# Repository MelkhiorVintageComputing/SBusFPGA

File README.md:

# A FPGA on a SBus card...

## Goal

The goal of this repository is to be able to interface a modern (2020 era) [FPGA](https://en.wikipedia.org/wiki/Field-programmable_gate_array) with a [SBus](https://en.wikipedia.org/wiki/SBus) host. SBus was widely used in SPARCstation and compatibles system in the first half of the 90s. It was progressively displaced by PCI from the mid-90s onward, and is thoroughly obsolete.

So unless you're a retrocomputing enthusiast with such a machine, this is useless. To be honest, even if you are such an enthusiast, it's probably not that useful...

I'm a software guy and know next to nothing about hardware design, so this is very much a work-in-progress and is likely full of rookie mistakes.

To save on PCB cost, the board is smaller than a 'true' SBus board; the hardware directory includes an OpenSCAD 3D-printable extension to make the board compliant to the form factor (visible in the pictures in 'Pictures') (need to be updated for V1.3).

## Current status

2023-10-07: V1.3 in testing.

2022-11-18: V1.2 seems stable, with various subsets of the peripherals described below. It only lacks a proper video output, such as the one available in the [NuBusFPGA](https://github.com/rdolbeau/NuBusFPGA). Unfortunately the FPGA board used in V1.0/V1.2 (ZTex 2.13) doesn't have enough available I/O to add it in addition to the already existing I/Os.

## The hardware

Directory 'sbus-to-ztex'

The V1.2 custom board is a SBus-compliant (I hope...) board, designed to receive a [ZTex USB-FPGA Module 2.13](https://www.ztex.de/usb-fpga-2/usb-fpga-2.13.e.html) as a daughterboard. The ZTex module contains the actual FPGA (Artix-7), some RAM, programming hardware, etc. The SBus board contains level-shifters ICs to interface between the SBus signals and the FPGA, a serial header, a Led, a JTAG header, a micro-sd card slot, a USB micro-B connector, and a (Pmod)[https://digilent.com/shop/boards-and-components/system-board-expansion-modules/pmods/] connector. It supports every SBus feature except the optional parity (i.e. it can do both slave and master modes) and interrupt level 1 to 6 are connected.

The V1.3 custom board is similar to V1.2 but reorganized & redesigned to have all components on the top side and cleaner routing. It also loose the led, setial header & micro-sd to gain a HDMI connector. The USB micro-B is still present, and the PMod was rewired to carry 8 length-matched differential pairs.

The PCB was designed with Kicad 5.0 for V1.2, 5.1 for V1.3.

## The gateware (Migen)

Directory 'sbus-to-ztex-gateware-migen'

### Intro

The gateware is written in the Migen language, choosen because that's what [Litex](https://github.com/enjoy-digital/litex/) uses.
It implements a simple CPU-less Litex SoC built around a Wishbone bus, with a custom bridge between the SBus and the Wishbone.

A ROM, a SDRAM controller ([litedram](https://github.com/enjoy-digital/litedram) to the on-board DDR3), a TRNG (using the [NeoRV32](https://github.com/stnolting/neorv32) TRNG), an USB OHCI (host controller, using the Litex wrapper around the [SpinalHDL](https://github.com/SpinalHDL/SpinalHDL) implementation), a Curve25519 Crypto Engine (taken from the [Betrusted.IO](https://betrusted.io/) project and expanded to add AES and GCM support) and a Litex micro-sd controller can be connected to that bus. As a test feature for the Pmod connector, a bw2/cg3/cg6-compatible framebuffer can be implemented using a custom RGA222 VGA Pmod (with serious color quality restrictions). The 'Goblin' framebuffer (a multi-depth gramebuffer) can also be used with the VGA Pmod, using 8-bits depth in the console or accelerated 24-bits in X11. Alternatively on the Pmod en I2C bus (the Betrusted.IO wrapper around an OpenCore controller) can be implemented for e.g. temperature control.

### Details

Master access to the SBus by the host are routed to the Wishbone to access the various CSRs / control registers of the devices.

The ROM exposes the devices' existence and specifications to the host, initializes the embedded SDRAM controller (but assuming known values, the NetBSD driver can also optionally initialize the SDRAM via proper calibration), enables FB support on the bw2/cg3/cg6 (last one with accelerated scrolling), and has support for RO access to the sdcard such enabling booting.

The USB OHCI DMA (USB 1.1) is bridged from the Wishbone to the SBus by having the physical addresses of the Wishbone (that match the virtual addresses from NetBSD DVMA allocations) to the bridge (see also 'Sun4m vs. Sun4c' below). Reads are buffered by block of 16 bytes; currently writes are unbuffered (and somewhat slow, as they need a full SBus master cycle for every transaction of 32 bits or less). The standard NetBSD OHCI driver is used, with just a small custom SBus-OHCI driver mirroring the PCI-OHCI one. It uses the interrupt level 4 by default. It connects to the micro-B USB connector, an a cable such as [this one](https://www.startech.com/en-us/cables/uusbotgra) allows to expose a conventional USB type A connector for either an external (preferably self-powered) USB Hub or a single low-power device.

The SDRAM has its own custom DMA controller, using native Litedram interface to the memory, and some FIFO to/from the SBus. A custom NetBSD driver exposes it as a drive on which you can swap. It's also usable as a 'fast', volatile disk (for e.g. /tmp or similar temporary filesystem). It can use a interrupt line, but software support isn't there yet (only synchronous polling).

The micro-sd card controller is using a similar driver to the SDRAM, so is also currently limited to sychronous polling and lack of support for interrupts (or removability). It also has some level of support in the PROM, enabling it as a boot device (of course using a NetBSD kernel with appropriate support). For its DMA engine, the micro-sd controller uses the same Wishbone/SBus bridge as designed for the USB OHCI.

The TRNG has a NetBSD driver to add entropy to the entropy pool.

The Curve25519 Engine currently exposes an IOCTL to do the computation, which has yet to be integrated usefully in e.g. OpenSSL. It could use a interrupt line, but it's not yet implemented in software. The load/store unit used the same Wishbone/SBus bridge as designed for the USB OHCI.

The I2C bus currently uses a custom Pmod to plug an AT30TS74 temperature sensor (LM75-compatible, usable with 'envstat' in NetBSD), but should support most/all I2C devices supported by NetBSD.

The bw2/cg3/cg6 emulation requires the custom Pmod on V1.2, and colors are vert limited at 2 bits per channel, so it's for testing mostly. V1.3 has a HDMI connector using DVI signaling and so support the full color range. bw2/cg3 can work as a PROM console, a NetBSD console, and with X11, all as an non-accelerated framebuffer. Resolution can be arbitrary but is fixed in the bitstream at synthesis time, the current design can go up to 1920x1080@60Hz. cg6 emulation is similar but uses a micro-coded VexRiscv core to emulate some of the cg6 hardware acceleration, enough to accelerate the PROM console, the NetBSD console and X11 EXA acceleration in NetBSD 9.0. The cg3/cg6 emulation was also tested with the original PROM code for cg3 (501-1415) and TGX+ (501-2253), but this requires hardware-based initialization (instead of PROM-based) and prevent exposing other devices in the PROM code.

The 'Goblin' framebuffer works similarly to the cg6 emulation (from which it has grown for the NuBusFPGA), but is using 24-bits in X11 (switching in a way similar to the cg14) and has some Xrender acceleration. Using the same 2-bits-per-channel VGA Pmod, it also suffers from color limitations ob V1.2. It also uses tje HDMI connector on V1.3.

### Special Notes

Currently the design uses a Wishbone Crossbar Interconnect from Litex instead of a Shared Interconnect, as for some reason using a Shared Interconnect causes issues between devices (disabling the USB OHCI seem also to solve the issue, it generates a lot of cycles on the buses). I might be misusing Wishbone. With the Crossbar, all devices are usable simultaneously if they fit in the FPGA.

As not everything lives in the same clock domain, the design also use a Wishbone CDC, a wrapper around the one from [Verilog Wishbone Components](https://github.com/alexforencich/verilog-wishbone).

## The software

Directory 'NetBSD'

Some basic drivers for NetBSD 9.0/sparc to enable the devices as described above. bw2/cg3/cg6 uses unmodifed NetBSD drivers. USB OHCI needs only a SBus-OHCI layer, the NetBSD OHCI driver and USB stack are used unmodified.

## Sun4m vs. Sun4c

The current DMA scheme for Wishbone devices (USB OHCI, micro-sd, ...) works fine on sun4m machine with an IOMMU (SPARCstation 4, 5, 10, 20 ...). NetBSD will always allocate the DVMA buffers in the range from IOMMU_DVMA_BASE to the end of the memory space (IOMMU_DVMA_BASE is 0xFC000000 by default, and that must include 0xFF000000 to the end which are the only virtual addresses accessible by some legacy devices used in some SPARCstation). However, sun4c machine (SPARCstation 1, 2, IPC, IPX, ...) do not have an IOMMU, and have no virtual address restriction for non-legacy device. And the NetBSD kernel takes advantage of this, I have observed DVMA buffers mapped to prefix 0xF4 and 0xF3. Extending the mapping for the DVMA bridge in Wishbone to the full 0xF prefix enable booting from sd-card on an IPX, but I'm not sure this is reliable.

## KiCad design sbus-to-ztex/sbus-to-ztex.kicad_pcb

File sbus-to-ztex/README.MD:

# A FPGA on a SBus card...

## Goal

The goal of this repository is to be able to interface a modern (2020 era) [FPGA](https://en.wikipedia.org/wiki/Field-programmable_gate_array) with a [SBus](https://en.wikipedia.org/wiki/SBus) host. SBus was widely used in SPARCstation and compatibles system in the first halt of the 90s. It was progressively displaced by PCI from the mid-90s onward.

So unless you're a retrocomputing enthusiast with such a machine, this is useless. To be honest, even if you are such an enthusiast, it's probably not that useful...

I'm a software guy and know next to nothing about hardware design, so this is very much a work-in-progress and is likely full of rookie mistakes.

## The hardware

The board is a SBus-compliant (I hope...) board, designed to receive a ZTex USB-FPGA Module 2.13 as a dauguterboard. The ZTex module contains the actual FPGA (Artix-7), some RAM, programming hardware, etc. The SBus board contains level-shifters ICs to interface between the SBus signals and the FPGA, some Leds, a JTAG header, and a micro-sd card slot.

## The gateware

The function embedded in the FPGA currently includes the PROM, lighting Led to display a 32-bits value, and a GHASH MAC (128 polynomial accumulator, used for the AES-GCM encryption scheme). The device is a fairly basic scale, but should be able to read from the PROM and read/write from the GCM space with any kind of SBus burst (1, 2, 4, 8 or 16 words).

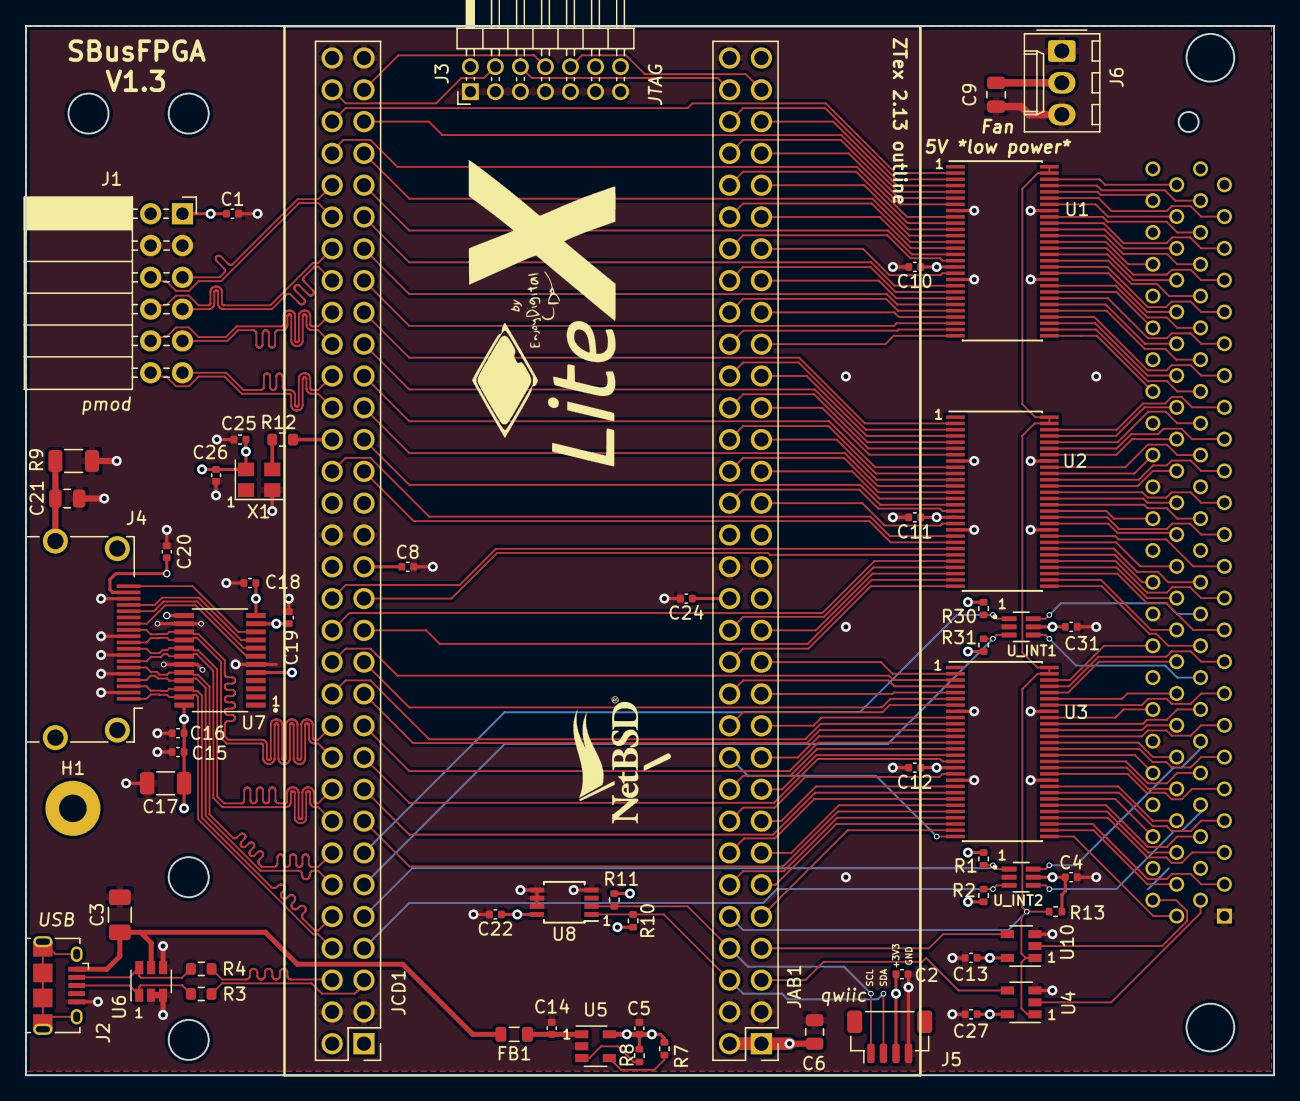
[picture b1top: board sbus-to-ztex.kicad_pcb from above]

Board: 4 copper layers, 99.7 x 83.8 mm, 64 parts (1 on the bottom side), 199 nets.

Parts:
C1, C2: 100nF; C_0402_1005Metric
C3: 100uF 1206 (officially 150 uF ? could be >= 100 u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; C_1206_3216Metric
C4, C5, C8, C10, C11, C12, C13, C14, C15, C18, C19, C20, C24, C25, C27, C31: 100nF 0402; C_0402_1005Metric
C6, C9: 47uF 0805; C_0805_2012Metric
C16, C22, C26: 10nF 0402; C_0402_1005Metric
C17: 47uF 10V 1206; C_1206_3216Metric
C21: 10nF 1kV 0805; C_0805_2012Metric
FB1: Ferrite_Bead_Small; L_0805_2012Metric
GRAPHIC1: LogoLitex; litex_logo
GRAPHIC2: LogoNetBSD; netbsd_logo
H1: MountingHole_Pad; MountingHole_2.2mm_M2_Pad
J1: A2541HWR-2x6P (Pmod 2x6 F R); PinSocket_2x06_P2.54mm_Horizontal
J2: 10118194-0001LF (USB micro-B); USB_Micro-B_Amphenol_10118194_Horizontal
J3: Conn_02x07_Odd_Even; PinHeader_2x07_P2.00mm_Horizontal_For_SeeedStudio
J4: 10029449-111RLF (HDMI A); HDMI_A_Amphenol_10029449-111
J5: Conn_01x04_Male; JST_SH_BM04B-SRSS-TB_1x04-1MP_P1.00mm_Vertical
J6: Conn_01x03_Male; Molex_KK-254_AE-6410-03A_1x03_P2.54mm_Vertical
JAB1: ZTEX_AB-ztex_AB; PinHeader_2x32_P2.54mm_Vertical_For_SeeedStudio
JCD1: ZTEX_CD-ztex_CD; PinHeader_2x32_P2.54mm_Vertical_For_SeeedStudio
R1, R2, R7, R8, R13, R30, R31: 10k; R_0402_1005Metric
R3, R4, R12: 27; R_0603_1608Metric
R9: 1M 500V 1206; R_1206_3216Metric
R10, R11: 5.6k; R_0402_1005Metric
SBus1: SBus; FCN-234P096-GY
U1, U2, U3: SN74CB3T16211DGGR; TSSOP-56_6.1x14mm_P0.5mm_For_SeeedStudio
U4, U10: 74CB3T1G125; SOT-23-5
U5: TPS2051CDBV; SOT-23-5
U6: SRV05-4; SOT-23-6
U7: TPD12S016PWR; SOP65P640X120-24N
U8: PCT2075DP; TSSOP-8_3x3mm_P0.65mm_ForSeeedStudio
U_INT1, U_INT2: 74LVC2G07; SOT65P210X110-6N
X1: ASE-xxxMHz; Oscillator_SMD_Abracon_ASE-4Pin_3.2x2.5mm

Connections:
+3V3: C1.1, C2.1, C4.1, C8.1, C10.1, C11.1, C12.1, C13.1, C15.1, C16.1, C17.1, C18.1, C22.1, C24.1, C25.1, C26.1, C27.1, C31.1, J1.1, J1.2, J5.3, JAB1.29, JAB1.30, JAB1.33, JAB1.34, JCD1.31, JCD1.32, JCD1.35, JCD1.36, R1.1, R2.1, R10.2, R11.2, R13.1, R30.1, R31.1, U1.17, U2.17, U3.17, U4.5, U7.5, U7.12, U7.24, U8.8, U10.5, U_INT1.5, U_INT2.5, X1.4
+5V: C5.1, C6.1, C9.1, C19.1, J6.2, JAB1.1, JAB1.2, R7.2, R8.2, SBus1.56, SBus1.64, SBus1.72, SBus1.80, SBus1.88, U5.5, U7.11
/B2B/JTAG_TCK: J3.6, JAB1.62
/B2B/JTAG_TDI: J3.10, JAB1.61
/B2B/JTAG_TDO: J3.8, JCD1.61
/B2B/JTAG_TMS: J3.4, JCD1.62
/B2B/JTAG_VIO: J3.2, JAB1.63
/USB/USB_D+: J2.3, R3.1, U6.1
/USB/USB_D-: J2.2, R4.1, U6.6
/USB/USB_EN: R7.1, U5.4
/USB/USB_FLT: R8.1, U5.3
/USB/VBus: C14.1, FB1.1, U5.1
/USB/VBus_USB0: C3.1, FB1.2, J2.1, U6.5
/hdmi/HDMI_5V: C20.1, J4.18, U7.13
/hdmi/cec_b: J4.13, U7.7
/hdmi/hpd_b: J4.19, U7.10
/hdmi/scl_b: J4.15, U7.8
/hdmi/sda_b: J4.16, U7.9
CLK_54_000: JCD1.40, R12.1
GND: C1.2, C2.2, C3.2, C4.2, C5.2, C6.2, C8.2, C9.2, C10.2, C11.2, C12.2, C13.2, C14.2, C15.2, C16.2, C17.2, C18.2, C19.2, C20.2, C21.2, C22.2, C24.2, C25.2, C26.2, C27.2, C31.2, J1.3, J1.4, J2.5, J3.1, J3.3, J3.5, J3.7, J3.9, J3.11, J3.13, J4.2, J4.5, J4.8, J4.11, J4.17, J5.4, J6.1, J6.3, JAB1.3, JAB1.4, JAB1.31, JAB1.32, JAB1.64, JCD1.3, JCD1.4, JCD1.33, JCD1.34, JCD1.63, JCD1.64, R9.2, SBus1.01, SBus1.52, SBus1.60, SBus1.68, SBus1.76, SBus1.84, SBus1.92, U1.8, U1.19, U1.38, U1.49, U2.8, U2.19, U2.38, U2.49, U3.8, U3.19, U3.38, U3.49, U4.3, U5.2, U6.2, U6.3, U6.4, U7.6, U7.14, U7.19, U8.4, U8.5, U8.6, U8.7, U10.3, U_INT1.2, U_INT2.2, X1.2
HDMI_CLK+: J4.10, JCD1.20, U7.16
HDMI_CLK-: J4.12, JCD1.22, U7.15
HDMI_D0+: J4.7, JCD1.16, U7.18
HDMI_D0-: J4.9, JCD1.18, U7.17
HDMI_D1+: J4.4, JCD1.12, U7.21
HDMI_D1-: J4.6, JCD1.14, U7.20
HDMI_D2+: J4.1, JCD1.8, U7.23
HDMI_D2-: J4.3, JCD1.10, U7.22
I2C0_SCL: J5.1, JAB1.8, R11.1, U8.2
I2C0_SDA: J5.2, JAB1.6, R10.1, U8.1
unnamed: R12.2, X1.3
PMOD-56+: J1.6, JCD1.54
PMOD-56-: J1.5, JCD1.56
PMOD-78+: J1.8, JCD1.52
PMOD-78-: J1.7, JCD1.50
PMOD-910+: J1.10, JCD1.48
PMOD-910-: J1.9, JCD1.46
PMOD-1112+: J1.12, JCD1.42
PMOD-1112-: J1.11, JCD1.44
SBUS_3V3_ACK[0]*: JAB1.48, U1.24
SBUS_3V3_ACK[1]*: JCD1.55, U1.15
SBUS_3V3_ACK[2]*: JAB1.57, U1.7
SBUS_3V3_AS*: JAB1.9, U3.27
SBUS_3V3_BG*: JAB1.7, U10.4
SBUS_3V3_BR*: JAB1.5, U4.4
SBUS_3V3_CLK: JAB1.20, U3.28
SBUS_3V3_D[00]: JAB1.12, U3.25
SBUS_3V3_D[01]: JCD1.15, U3.24
SBUS_3V3_D[02]: JAB1.13, U3.23
SBUS_3V3_D[03]: JAB1.14, U3.22
SBUS_3V3_D[04]: JCD1.17, U3.21
SBUS_3V3_D[05]: JAB1.15, U3.20
SBUS_3V3_D[06]: JAB1.16, U3.18
SBUS_3V3_D[07]: JCD1.19, U3.16
SBUS_3V3_D[08]: JAB1.17, U3.15
SBUS_3V3_D[09]: JAB1.18, U3.14
SBUS_3V3_D[10]: JCD1.21, U3.13
SBUS_3V3_D[11]: JAB1.19, U3.12
SBUS_3V3_D[12]: JCD1.23, U3.11
SBUS_3V3_D[13]: JCD1.24, U3.10
SBUS_3V3_D[14]: JAB1.21, U3.9
SBUS_3V3_D[15]: JAB1.22, U3.7
SBUS_3V3_D[16]: JCD1.25, U3.6
SBUS_3V3_D[17]: JAB1.23, U3.5
SBUS_3V3_D[18]: JAB1.24, U3.4
SBUS_3V3_D[19]: JCD1.26, U3.3
SBUS_3V3_D[20]: JAB1.25, U3.2
SBUS_3V3_D[21]: JAB1.26, U2.28
SBUS_3V3_D[22]: JCD1.27, U2.27
SBUS_3V3_D[23]: JAB1.27, U2.26
SBUS_3V3_D[24]: JAB1.28, U2.25
SBUS_3V3_D[25]: JCD1.28, U2.24
SBUS_3V3_D[26]: JCD1.29, U2.23
SBUS_3V3_D[27]: JCD1.30, U2.22
SBUS_3V3_D[28]: JCD1.37, U2.21
SBUS_3V3_D[29]: JCD1.38, U2.20
SBUS_3V3_D[30]: JAB1.35, U2.18
SBUS_3V3_D[31]: JAB1.36, U2.16
SBUS_3V3_EER*: JAB1.43, U2.4
SBUS_3V3_INT[2]*: JCD1.7, R2.2, U_INT2.3
SBUS_3V3_INT[3]*: JCD1.9, R1.2, U_INT2.1
SBUS_3V3_INT[4]*: JCD1.11, R31.2, U_INT1.3
SBUS_3V3_INT[5]*: JCD1.13, R30.2, U_INT1.1
SBUS_3V3_PA[00]: JAB1.40, U2.10
SBUS_3V3_PA[01]: JAB1.39, U2.11
SBUS_3V3_PA[02]: JAB1.41, U2.7
SBUS_3V3_PA[03]: JCD1.43, U2.9
SBUS_3V3_PA[04]: JCD1.45, U2.5
SBUS_3V3_PA[05]: JAB1.42, U2.6
SBUS_3V3_PA[06]: JCD1.47, U2.2
SBUS_3V3_PA[07]: JAB1.44, U2.3
SBUS_3V3_PA[08]: JAB1.46, U1.27
SBUS_3V3_PA[09]: JAB1.45, U1.28
SBUS_3V3_PA[10]: JAB1.47, U1.25
SBUS_3V3_PA[11]: JCD1.49, U1.26
SBUS_3V3_PA[12]: JAB1.49, U1.22
SBUS_3V3_PA[13]: JCD1.51, U1.23
SBUS_3V3_PA[14]: JCD1.53, U1.20
SBUS_3V3_PA[15]: JAB1.50, U1.21
SBUS_3V3_PA[16]: JAB1.52, U1.16
SBUS_3V3_PA[17]: JAB1.51, U1.18
SBUS_3V3_PA[18]: JAB1.54, U1.13
SBUS_3V3_PA[19]: JAB1.53, U1.14
SBUS_3V3_PA[20]: JAB1.55, U1.11
SBUS_3V3_PA[21]: JCD1.57, U1.12
SBUS_3V3_PA[22]: JCD1.58, U1.9
SBUS_3V3_PA[23]: JAB1.56, U1.10
SBUS_3V3_PA[24]: JCD1.59, U1.5
SBUS_3V3_PA[25]: JAB1.58, U1.6
SBUS_3V3_PA[26]: JAB1.60, U1.3
SBUS_3V3_PA[27]: JAB1.59, U1.4
SBUS_3V3_PPRD: JAB1.38, U2.13
SBUS_3V3_RST*: JCD1.60, U1.2
SBUS_3V3_SEL*: JAB1.11, U3.26
SBUS_3V3_SIZ[0]: JAB1.37, U2.14
SBUS_3V3_SIZ[1]: JCD1.39, U2.15
SBUS_3V3_SIZ[2]: JCD1.41, U2.12
SBUS_5V_ACK[0]*: SBus1.36, U1.33
SBUS_5V_ACK[1]*: SBus1.40, U1.41
SBUS_5V_ACK[2]*: SBus1.44, U1.48
SBUS_5V_AS*: SBus1.51, U3.30
SBUS_5V_BG*: SBus1.50, U10.2
SBUS_5V_BR*: SBus1.02, U4.2
SBUS_5V_CLK: SBus1.49, U3.29
SBUS_5V_D[00]: SBus1.05, U3.32
SBUS_5V_D[01]: SBus1.53, U3.33
SBUS_5V_D[02]: SBus1.06, U3.34
SBUS_5V_D[03]: SBus1.54, U3.35
SBUS_5V_D[04]: SBus1.07, U3.36
SBUS_5V_D[05]: SBus1.55, U3.37
SBUS_5V_D[06]: SBus1.09, U3.39
SBUS_5V_D[07]: SBus1.57, U3.40
SBUS_5V_D[08]: SBus1.10, U3.41
SBUS_5V_D[09]: SBus1.58, U3.42
SBUS_5V_D[10]: SBus1.11, U3.43
SBUS_5V_D[11]: SBus1.59, U3.44
SBUS_5V_D[12]: SBus1.13, U3.45
SBUS_5V_D[13]: SBus1.61, U3.46
SBUS_5V_D[14]: SBus1.14, U3.47
SBUS_5V_D[15]: SBus1.62, U3.48
SBUS_5V_D[16]: SBus1.15, U3.50
SBUS_5V_D[17]: SBus1.63, U3.51
SBUS_5V_D[18]: SBus1.65, U3.52
SBUS_5V_D[19]: SBus1.17, U3.53
SBUS_5V_D[20]: SBus1.66, U3.54
SBUS_5V_D[21]: SBus1.18, U2.29
SBUS_5V_D[22]: SBus1.67, U2.30
SBUS_5V_D[23]: SBus1.19, U2.31
SBUS_5V_D[24]: SBus1.69, U2.32
SBUS_5V_D[25]: SBus1.21, U2.33
SBUS_5V_D[26]: SBus1.70, U2.34
SBUS_5V_D[27]: SBus1.22, U2.35
SBUS_5V_D[28]: SBus1.71, U2.36
SBUS_5V_D[29]: SBus1.23, U2.37
SBUS_5V_D[30]: SBus1.73, U2.39
SBUS_5V_D[31]: SBus1.25, U2.40
SBUS_5V_EER*: SBus1.32, U2.52
SBUS_5V_INT[2]*: SBus1.08, U_INT2.4
SBUS_5V_INT[3]*: SBus1.12, U_INT2.6
SBUS_5V_INT[4]*: SBus1.16, U_INT1.4
SBUS_5V_INT[5]*: SBus1.20, U_INT1.6
SBUS_5V_PA[00]: SBus1.29, U2.46
SBUS_5V_PA[01]: SBus1.77, U2.45
SBUS_5V_PA[02]: SBus1.30, U2.48
SBUS_5V_PA[03]: SBus1.78, U2.47
SBUS_5V_PA[04]: SBus1.31, U2.51
SBUS_5V_PA[05]: SBus1.79, U2.50
SBUS_5V_PA[06]: SBus1.33, U2.54
SBUS_5V_PA[07]: SBus1.81, U2.53
SBUS_5V_PA[08]: SBus1.34, U1.30
SBUS_5V_PA[09]: SBus1.82, U1.29
SBUS_5V_PA[10]: SBus1.35, U1.32
SBUS_5V_PA[11]: SBus1.83, U1.31
SBUS_5V_PA[12]: SBus1.37, U1.35
SBUS_5V_PA[13]: SBus1.85, U1.34
SBUS_5V_PA[14]: SBus1.38, U1.37
SBUS_5V_PA[15]: SBus1.86, U1.36
SBUS_5V_PA[16]: SBus1.39, U1.40
SBUS_5V_PA[17]: SBus1.87, U1.39
SBUS_5V_PA[18]: SBus1.41, U1.43
SBUS_5V_PA[19]: SBus1.89, U1.42
SBUS_5V_PA[20]: SBus1.42, U1.45
SBUS_5V_PA[21]: SBus1.90, U1.44
SBUS_5V_PA[22]: SBus1.43, U1.47
SBUS_5V_PA[23]: SBus1.91, U1.46
SBUS_5V_PA[24]: SBus1.45, U1.51
SBUS_5V_PA[25]: SBus1.93, U1.50
SBUS_5V_PA[26]: SBus1.46, U1.53
SBUS_5V_PA[27]: SBus1.94, U1.52
SBUS_5V_PPRD: SBus1.75, U2.43
SBUS_5V_RST*: SBus1.95, U1.54
SBUS_5V_SEL*: SBus1.03, U3.31
SBUS_5V_SIZ[0]: SBus1.26, U2.42
SBUS_5V_SIZ[1]: SBus1.74, U2.41
SBUS_5V_SIZ[2]: SBus1.27, U2.44
SBUS_OE: JAB1.10, R13.2, U1.55, U1.56, U2.55, U2.56, U3.55, U3.56, U4.1, U10.1
SHIELD: C21.1, H1.1, J2.6, J4.SH, R9.1
USBH0_D+: JCD1.5, R3.2
USBH0_D-: JCD1.6, R4.2

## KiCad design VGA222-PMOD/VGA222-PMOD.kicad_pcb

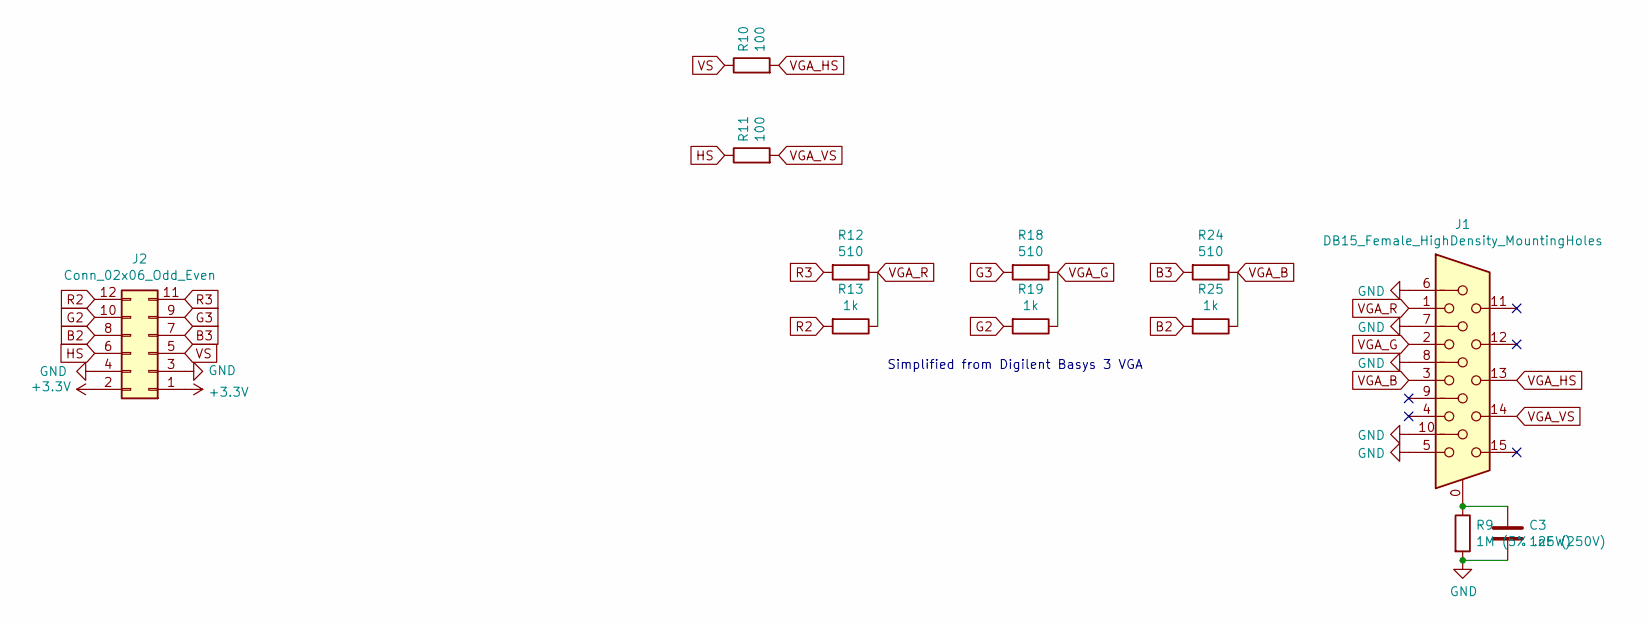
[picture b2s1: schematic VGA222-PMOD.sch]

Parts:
C3: 1nF (250V); CP_Radial_D6.3mm_P2.50mm; MPN 860021373002
J1: DB15_Female_HighDensity_MountingHoles; L77HDE15SD1CH4RHNVGA; MPN L77HDE15SD1CH4RHNVGA
J2: Conn_02x06_Odd_Even; PinHeader_2x06_P2.54mm_Horizontal; MPN A2541WR-2x6P
R9: 1M (5% .25W); R_Axial_DIN0207_L6.3mm_D2.5mm_P2.54mm_Vertical; MPN MFR50SFTE52-1M
R10, R11: 100; R_Axial_DIN0207_L6.3mm_D2.5mm_P2.54mm_Vertical; MPN-ALT MFR-25FTE52-100R
R12, R18, R24: 510; R_Axial_DIN0207_L6.3mm_D2.5mm_P2.54mm_Vertical; MPN MFR-25FTE52-510R
R13, R19, R25: 1k; R_Axial_DIN0207_L6.3mm_D2.5mm_P2.54mm_Vertical; MPN-ALT MFR-25FTE52-1K

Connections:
+3V3: J2.1, J2.2
B2: J2.8, R25.2
B3: J2.7, R24.2
G2: J2.10, R19.2
G3: J2.9, R18.2
GND: C3.2, J1.5, J1.6, J1.7, J1.8, J1.10, J2.3, J2.4, R9.2
HS: J2.6, R11.1
unnamed: C3.1, J1.0, R9.1
R2: J2.12, R13.2
R3: J2.11, R12.2
VGA_B: J1.3, R24.1, R25.1
VGA_G: J1.2, R18.1, R19.1
VGA_HS: J1.13, R10.2
VGA_R: J1.1, R12.1, R13.1
VGA_VS: J1.14, R11.2
VS: J2.5, R10.1

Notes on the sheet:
Simplified from Digilent Basys 3 VGA

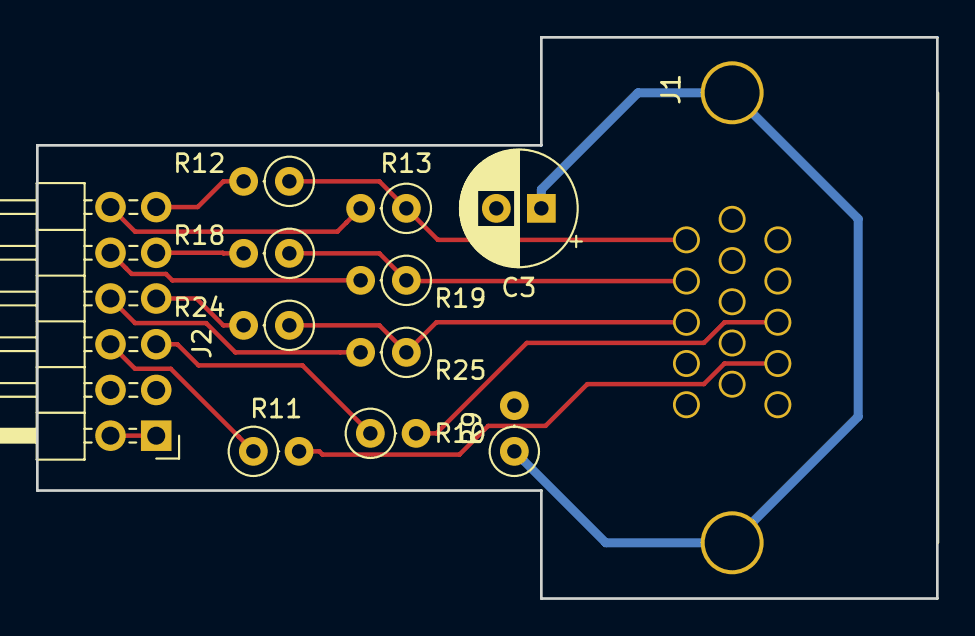
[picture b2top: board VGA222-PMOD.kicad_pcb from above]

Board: 2 copper layers, 50.0 x 31.2 mm, 12 parts (0 on the bottom side), 16 nets.

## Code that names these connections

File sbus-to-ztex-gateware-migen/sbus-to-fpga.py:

import os
import argparse
from migen import *
import litex
from litex.build.generic_platform import *
from litex.build.xilinx.vivado import vivado_build_args, vivado_build_argdict
from litex.soc.integration.soc import *
from litex.soc.integration.soc_core import *
from litex.soc.integration.builder import *
from litex.soc.cores.clock import *
from litex.soc.cores.led import LedChaser
from litex_boards.platforms import ztex213
from migen.genlib.fifo import *

from sbus_to_fpga_slave import *;
from sbus_to_fpga_wishbone import *;

_sbus_sbus = [
    ("SBUS_3V3_CLK",       0, Pins("D15"), IOStandard("lvttl")),
    ("SBUS_3V3_ASs",       0, Pins("T4"),  IOStandard("lvttl")),
    ("SBUS_3V3_BGs",       0, Pins("T6"),  IOStandard("lvttl")),
    ("SBUS_3V3_BRs",       0, Pins("R6"),  IOStandard("lvttl")),
    ("SBUS_3V3_ERRs",      0, Pins("V2"),  IOStandard("lvttl")),
    ("SBUS_DATA_OE_LED",   0, Pins("U1"),  IOStandard("lvttl")),
    ("SBUS_DATA_OE_LED_2", 0, Pins("T3"),  IOStandard("lvttl")),
    ("SBUS_3V3_RSTs",      0, Pins("U2"),  IOStandard("lvttl")),
    ("SBUS_3V3_SELs",      0, Pins("K6"),  IOStandard("lvttl")),
    ("SBUS_3V3_INT1s",     0, Pins("R3"),  IOStandard("lvttl")),
    ("SBUS_3V3_INT7s",     0, Pins("N5"),  IOStandard("lvttl")),
    ("SBUS_3V3_PPRD",      0, Pins("N6"),  IOStandard("lvttl")),
    ("SBUS_OE",            0, Pins("P5"),  IOStandard("lvttl")),
    ("SBUS_3V3_ACKs",      0, Pins("M6 L6 N4"),  IOStandard("lvttl")),
    ("SBUS_3V3_SIZ",       0, Pins("R7 U3 V1"),  IOStandard("lvttl")),
    ("SBUS_3V3_D",         0, Pins("J18 K16 J17 K15 K13 J15 J13 J14 H14 H17 G14 G17 G16 G18 H16 F18 F16 E18 F15 D18 E17 G13 D17 F13 F14 E16 E15 C17 C16 A18 B18 C15"),  IOStandard("lvttl")),
    ("SBUS_3V3_PA",        0, Pins("B16 B17 D14 C14 D12 A16 A15 B14 B13 B12 C12 A14 A13 B11 A11  M4  R2  M3  P2  M2  N2  K5  N1  L4  M1  L3  L1  K3"),  IOStandard("lvttl")),
]
# CRG ----------------------------------------------------------------------------------------------

class _CRG(Module):
    def __init__(self, platform, sys_clk_freq):
        self.clock_domains.cd_sys       = ClockDomain()
        self.clock_domains.cd_native    = ClockDomain(reset_less=True)
        self.clock_domains.cd_sbus      = ClockDomain()
        self.clock_domains.cd_por       = ClockDomain()

        # # #
        clk48 = platform.request("clk48")
        self.cd_native.clk = clk48
        clk_sbus = platform.request("SBUS_3V3_CLK")
        self.cd_sbus.clk = clk_sbus
        rst_sbus = platform.request("SBUS_3V3_RSTs")

        self.comb += self.cd_sbus.rst.eq(~rst_sbus)

        self.submodules.pll = pll = S7MMCM(speedgrade=-1)
        pll.register_clkin(clk48, 48e6)
        pll.create_clkout(self.cd_sys, sys_clk_freq)

        platform.add_false_path_constraints(self.cd_native.clk, self.cd_sbus.clk)
        platform.add_false_path_constraints(self.cd_sys.clk, self.cd_sbus.clk)
        platform.add_false_path_constraints(self.cd_sbus.clk, self.cd_native.clk)
        platform.add_false_path_constraints(self.cd_sbus.clk, self.cd_sys.clk)
        
        # Power on reset, reset propagate from SBus to SYS
        por_count = Signal(16, reset=2**16-1)
        por_done  = Signal()
        self.comb += self.cd_por.clk.eq(clk48)
        self.comb += por_done.eq(por_count == 0)
        self.sync.por += If(~por_done, por_count.eq(por_count - 1))
        self.comb += pll.reset.eq(~por_done | ~rst_sbus)
        
class SBusFPGA(SoCCore):
    def __init__(self, **kwargs):

        kwargs["cpu_type"] = "None"
        kwargs["integrated_sram_size"] = 0
        kwargs["with_uart"] = True
        kwargs["with_timer"] = False
        
        self.sys_clk_freq = sys_clk_freq = 100e6
    
        self.platform = platform = ztex213.Platform(variant="ztex2.13a", expansion="sbus")
        self.platform.add_extension(_sbus_sbus)
        SoCCore.__init__(self, platform=platform, sys_clk_freq=sys_clk_freq, clk_freq=sys_clk_freq, **kwargs)
        wb_mem_map = {
            "prom": 0x00000000,
            "csr" : 0x00040000,
        }
        self.mem_map.update(wb_mem_map)
        self.submodules.crg = _CRG(platform=platform, sys_clk_freq=sys_clk_freq)
        self.platform.add_period_constraint(self.platform.lookup_request("SBUS_3V3_CLK", loose=True), 1e9/25e6) # SBus max

        self.submodules.leds = LedChaser(
            pads         = platform.request_all("user_led"),
            sys_clk_freq = sys_clk_freq)
        self.add_csr("leds")

        prom_file = "prom_mini.fc"
        prom_data = soc_core.get_mem_data(prom_file, "big")
        prom = Array(prom_data)
        #print("\n****************************************\n")
        #for i in range(len(prom)):
        #    print(hex(prom[i]))
        #print("\n****************************************\n")
        self.add_ram("prom", origin=self.mem_map["prom"], size=2**16, contents=prom_data, mode="r") # for show
        #getattr(self,"prom").mem.init = prom_data
        #getattr(self,"prom").mem.depth = 2**14

        # don't enable anything on the SBus side for 20 seconds after power up
        # this avoids FPGA initialization messing with the cold boot process
        # requires us to reset the SPARCstation afterward so the FPGA board
        # is properly identified
        # This is in the 'native' ClockDomain that is never reset
        hold_reset_ctr = Signal(30, reset=960000000)
        self.sync.native += If(hold_reset_ctr>0, hold_reset_ctr.eq(hold_reset_ctr - 1))
        hold_reset = Signal(reset=1)
        self.comb += hold_reset.eq(~(hold_reset_ctr == 0))

        

        
        sbus_to_wishbone_wr_fifo = AsyncFIFOBuffered(width=32+30, depth=16)
        sbus_to_wishbone_wr_fifo = ClockDomainsRenamer({"write": "sbus", "read": "sys"})(sbus_to_wishbone_wr_fifo)
        self.submodules += sbus_to_wishbone_wr_fifo
        
        sbus_to_wishbone_rd_fifo_addr = AsyncFIFOBuffered(width=30, depth=16)
        sbus_to_wishbone_rd_fifo_addr = ClockDomainsRenamer({"write": "sbus", "read": "sys"})(sbus_to_wishbone_rd_fifo_addr)
        self.submodules += sbus_to_wishbone_rd_fifo_addr
        sbus_to_wishbone_rd_fifo_data = AsyncFIFOBuffered(width=32, depth=16)
        sbus_to_wishbone_rd_fifo_data = ClockDomainsRenamer({"write": "sys", "read": "sbus"})(sbus_to_wishbone_rd_fifo_data)
        self.submodules += sbus_to_wishbone_rd_fifo_data
        
        self.submodules.sbus_to_wishbone = SBusToWishbone(wr_fifo=sbus_to_wishbone_wr_fifo,
                                                          rd_fifo_addr=sbus_to_wishbone_rd_fifo_addr,
                                                          rd_fifo_data=sbus_to_wishbone_rd_fifo_data,
                                                          wishbone=wishbone.Interface(data_width=self.bus.data_width))

        _sbus_slave = SBusFPGASlave(platform=self.platform,
                                    prom=prom,
                                    hold_reset=hold_reset,
                                    wr_fifo=sbus_to_wishbone_wr_fifo,
                                    rd_fifo_addr=sbus_to_wishbone_rd_fifo_addr,
                                    rd_fifo_data=sbus_to_wishbone_rd_fifo_data,)
        self.submodules.sbus_slave = ClockDomainsRenamer("sbus")(_sbus_slave)

        self.bus.add_master(name="SBusBridgeToWishbone", master=self.sbus_to_wishbone.wishbone)
        
 #       self.soc = Module()
 #       self.soc.mem_regions = self.mem_regions = {}
 #       region = litex.soc.integration.soc.SoCRegion(origin=0x0, size=0x0)
 #       region.length = 0
 #       self.mem_regions['csr'] = region
 #       self.soc.constants = self.constants = {}
 #       self.soc.csr_regions = self.csr_regions = {}
 #       self.soc.cpu_type = self.cpu_type = None

#    def do_finalize(self):
#        self.platform.add_period_constraint(self.platform.lookup_request("SBUS_3V3_CLK", loose=True), 1e9/25e6)

def main():
    parser = argparse.ArgumentParser(description="SbusFPGA")
    parser.add_argument("--build", action="store_true", help="Build bitstream")
    builder_args(parser)
    vivado_build_args(parser)
    args = parser.parse_args()
    
    soc = SBusFPGA(**soc_core_argdict(args))
    #soc.add_uart(name="uart", baudrate=115200, fifo_depth=16)
    
    builder = Builder(soc, **builder_argdict(args))
    builder.build(**vivado_build_argdict(args), run=args.build)

if __name__ == "__main__":
    main()

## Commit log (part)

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2020-12-13 Add the sbus-to-zex adapter board
2020-12-13 Add the sbus-to-zex gateware
2020-12-13 Pictures
2020-12-13 NetBSD prototype driver
2020-12-13 move/update README
2020-12-13 using 8 bytes functions seems a bit faster overall (but the host still use 32 bits transfers)
2020-12-13 Add write() support for I, much faster than going through ioctl 16 bytes at a time...
2020-12-14 fix names, add new picture
2020-12-15 disable COUNTER25 heartbeat, remove superfluous state in the FSM (detecting ACK is handled by a variable instead)
2020-12-16 LEDs show that the board has been probed
2020-12-16 cleanup
2020-12-16 change ROM 'LEDs show that the board has been probed'
2020-12-16 more comments
2020-12-16 Improve reset (?), add IOBUF on some signals that are INOUT when including 'master' mode (but not yet Extended Transfer for which 'master' is a pretty much a prerequisite)
2020-12-16 add some extra registers for potential DMA
2020-12-17 ultra-preliminary support for a bus master DMA)
2020-12-18 basic DMA support
2020-12-18 disable tracing
2020-12-18 only alloc/map/load once per write()
2020-12-18 12 bits of blocks in GCM DMA
2020-12-18 larger DMA burst (Burst16 disabled, as it doesn't work on the SS20, presumably hitting the limit of the 'up-burst-sizes' attribute https://mail-index.netbsd.org/port-sparc/2020/12/18/msg002291.html)
2020-12-18 new prom
2020-12-19 unify LED register with others
2020-12-20 Adding basic AES support (using AES block from https://github.com/mbgh/aes128-hdl)
2020-12-21 switch driver code to basic aes128-cbc support, where openssl and devcrypto are in agreement
2020-12-21 enable the XOR in HW for CBC mode, some R/W protect on registers
2020-12-22 DMA busmaster AES-128-CBC
2020-12-22 Move the AES block to https://github.com/secworks/aes (slower at this time, but has decrypt & 256 bits support)
2021-01-03 Move CTRLs registers around, add 4 key registers/preliminary HW support for AES256
2021-01-03 aes-256-cbc
2021-01-03 try multi-sessions; there could be a race condition for keys, and device is too busy leading to failure...
2021-01-03 fix multi-session
2021-01-09 encdec signal for AS (unused)
2021-01-09 add timing constraints for master signals
2021-01-09 constant-ify
2021-01-09 split AES DMA in two control registers (for future pipelining?)
2021-01-09 PIO decrypt of CBC
2021-01-09 DMA for cbc decrypt
2021-01-09 more constants, more room for the prom
2021-01-09 new device name, trying to figure out how to have siblings device in the PROM
2021-01-09 Add a secondary driver for a pretend-trng (it's a prng at this stage, the trng I found won't synthesize)
2021-01-09 drop some old commented-out stuff
2021-01-09 reindent
2021-01-09 have a fisrst go at RDOL,sdcard (nor working) as a third device with the XESS sd-card controller.
2021-01-10 add 5 MHz timecounter to rdfpga_trng
2021-01-10 can read some blocks from sd-card, but then something fails and the wrapper won't acknowledge the rd_addr handshake :-(
2021-01-10 I|O -> IO for master
2021-01-10 fix sdcard read (cleanup needed)
2021-01-11 commit attempt at writing to sd-card, which has broken reading ?\!?
2021-01-12 oups, typo
2021-01-13 fix pullup
2021-01-13 parametrize timeout max
2021-01-17 nothing doing, SPI-mode SD won't work reliably :-(
2021-01-23 status
2021-01-23 aes256 ioctl
2021-01-23 byte-reverse in word for GCM
2021-01-24 HW post-increment of counter in AES for GCM
2021-02-28 error msg on timeout
2021-02-28 Userland SW bug :-(, seem to work now, disabling some debug stuuf
2021-03-16 save current status; can read label but not yet mount a partition...
2021-03-21 FAT now mount RO, to be tested more thoroughly
2021-06-13 PoC for Migen version of the SBus slave FSM; is recognized by PROM
2021-06-13 more stuff, with some weird bugs...
2021-06-13 grrrr, syntax
2021-06-14 more cleanups, Chaser still not going to control mode :-/
2021-06-15 Wishbone is word-addressed (still no lock)
2021-06-15 fix wishbone.sel, now the PROM can control the LEDs :-)
2021-06-15 Add a FIFO for CDC between SBus (in cd_sbus) and Wishbone (in a 100 MHz cd_sys)
2021-06-17 timeout to avoid hang when something on the wishbone is a bit slow
2021-06-19 still some issues on registers, master mode draft
2021-06-19 drop address mapping, simply map the NetBSd DVMA virtual space (?) as Wishbone physical address
2021-06-19 not working, the DMA seems to fails at frame 3...
2021-06-21 Still very wonkey, DMA burning cycles
2021-06-21 oups
2021-06-21 Byte support, needed; still need HWord...
2021-06-21 HWord support, needed
2021-06-23 swap endianness on flash prefix
2021-06-23 cleanups
2021-06-24 bring back cross-domain using a wishbone adapter
2021-06-25 DMA supports byte & hword (needed), identify devices but unstable
2021-06-27 configure the sdram; prom is not initializing it properly yet
2021-06-27 drop unused file
2021-06-30 Commit first go at v1.2
2021-06-30 Commit first go at v1.2 (updated BOM generator)
2021-06-30 fix footprints for SeeedStudio DRC results
2021-07-01 update some MPN w/ SeeedStudio replacement
2021-07-02 more stuff
2021-07-02 add a pwr header (for e.g. non-pwm fan)
2021-07-14 prom
2021-07-14 cleanup, CSR for prom & netbsd (preliminary)
2021-07-14 Forgotten-to-commit update
2021-07-14 driver to initialize the SDRAM (should be done in the PROM, but easier in C...)
2021-07-14 update prom
2021-07-14 read PROM from Wishbone (simplify things, save resources as it was mapped there already anyway), add sd_card (unused, un-promed yet)
2021-07-14 clean dmesg
2021-07-15 minor renaming, think about buffering writes
2021-07-18 Oups forgot the DMA engine (this version with wishbone Converter)
2021-07-18 blk dev/dk support for sbusfpga_sdram
2021-07-18 switch sdram access from Wishbone to dedicated port, seems to be more reliable
2021-07-18 swap on sbusfpga_sdram seems to work, but hogs the bus
2021-07-18 re-enable USB in PROM, make sure the SDRAM request don't inadvertently kill the USB request
2021-07-18 SBus-OHCI driver
2021-07-18 update READMEs
2021-07-20 commit the neorv32trgn-based trng
2021-07-24 driver update
2021-07-24 bytes not blocks
2021-07-24 SDRAM driver now complete enough to sunlabel/newfs
2021-07-25 Avoid some potential race conditions
2021-07-25 Trying to integrate Bestrusted's Curve25519 engine ; trivial program works but not after a few repetition :-(
2021-07-29 more tests
2021-08-21 add ioctls for testing
2021-08-21 (optional) checksumming in SDRAM DMA, change clocking on Engine, ...
2021-08-21 add an SBus statistics module (and discover a bug in the sbus lave timeouts and a lot of slave re-run)
2021-08-21 move the last errored address to sbusfpga_stat ; add missing stat driver
2021-08-22 Enable everything (using a Wishbone Crossbar instead of a Shared), some changes to Sbus timeouts, seems that everything play nice together now, also change Engine code to need fewer inputs
2021-08-22 CSRs don't support CDC... move Engine to sysclk ; also forgot to commit fsmstat
2021-08-23 ioctl on/off switch on stats + ctrl pgm
2021-08-25 commit the experimental GCM/AES stuff in the engine
2021-08-26 Full AES encrypt
2021-08-28 Fewer LEDs, more interrupts, replace USB VBus power chip by something that might be available..., update signals file
2021-08-28 USB ID pin left floating
2021-09-04 prelim work for V1.2
2021-09-04 preliminary work on AES256-GCM in the Engine
2021-09-04 prelim for boot-time support
2021-09-04 display all codes in engine_code
2021-09-04 USB configurability
2021-09-04 4 AES inst -> just 1
2021-09-05 Put AES in the mul_clk domain
2021-09-05 option to disable upper lane in AES/GCM isntructions; disable them in the code
2021-09-06 Loops are easier to read...
2021-09-06 more V1.2
2021-09-07 apply patch from betrusted-io/gateware commit 817e284a3d92037b8cb0686735578d2bb60853e9
2021-09-19 more V1.0 to V1.2 update stuff
2021-09-19 More V1.X stuff, still need to modularize the PROM. Also, why irqs other than 3 fails in Migen in V1.2 ???
2021-09-20 version-specific proms
2021-09-21 more ocnfigurability
2021-09-23 minor stuff
2021-09-23 bring back add_usb locally
2021-10-01 forgotten to commit extension for V1.0 with fan carrier
2021-10-03 start working on some form of how-to
2021-10-07 start working on some form of how-to, improve backplate for V1.2
2021-10-07 init sdram in PROM
2021-10-08 CG3 is usable as console and with X11, despite the ugly colors
2021-10-09 README in Pictures
2021-10-09 add a known limitation
2021-10-09 don't need the extra 256 KiB
2021-10-09 add VGA222 Pmod
2021-10-10 WB FSM was broken (cmap to be tested still)
2021-10-11 one more word of warning
2021-10-15 proto CG6
2021-10-24 Dcache-less Vex
2021-10-24 trying to improve the timing in the vga_clk domain
2021-10-30 move the wishbone CDC locally ; speedgrade from part
2021-10-30 fix broken timeout, some (disabled, for testing) stat stuff
2021-10-30 CG6 accel emulation (still slow)
2021-10-30 more improvements
2021-10-30 add a (working this time) Dcache to Vex
2021-10-30 extrac cycle to meet timings at 1920x1080@60 when using HW cursor
2021-10-30 more configuratble blit rom
2021-10-31 smaller vex
2021-10-31 minor changes
2021-11-01 Add FSR to Vex, use it for unaligned blits
2021-11-01 Add sext.b to Vex, as some are generated in -O2/-O3 (none in -Os)
2021-11-06 use fth cst
2021-11-06 fix checksum-less building
2021-11-06 comment
2021-11-07 add remove functions, doesn't help
2021-11-13 cleanup, preliminary sdcard driver
2021-11-13 drop V1.0
2021-11-13 fb stuff
2021-11-13 sdcard, interrupt line on sdram
2021-11-17 various updates, and prom driver for sdcard
2021-11-19 better sd(ram|card) drivers
2021-11-20 minor details, more non-working intr code
2021-11-20 upd readme
2021-12-05 record/layour for cmap/omap
2021-12-18 Emulate a bw2 FB, mostly to test feasibility of 1bpp FB in Litex
2021-12-19 Simple model of SBus retainer
2022-01-08 add support for alu/mode used by 501-2253/2325 PROMs
2022-01-25 fix sdram prom config for 90 MHz sysclk
2022-01-26 fix sdram prom config fix, drop DMA from the sdram DMA and talk to a native SDRAM port instead
2022-01-29 improve backplate
2022-01-29 preliminary i2c support via the OC I2C ctrl & betrustedio wrapper
    Now with a NetBSD driver (based on the OpenBSD one) that shows the i2c bus, and some prom support. Not tested with a device, waiting on custom Pmod.
2022-01-29 git ignore
2022-01-29 oups, forgotten files for DDR3 hardware initializer based on gist 529a4d9994f0cc95e45382e4eb253b09-3c8bb9c1f4528ccb0c0ef603d66f05b1470e8056
2022-01-29 ignore OLD stuff
2022-02-25 fix i2c support
2022-03-06 working on goblin
2022-03-08 preliminary goblin
2022-03-08 preliminary goblin X11
2022-03-11 first go at jareth-with-goblin
2022-03-12 add direct memory access support to Jareth UnitLS
2022-03-12 brz to brz32, erasecols in console
2022-03-13 16 MiB for Goblin
2022-03-13 more jareth-with-goblin
2022-03-16 more aceel
2022-03-18 more jareth
2022-03-20 forward port HW cursor from cg6, still some issues (sw or hw???) + untested sw fix
2022-03-27 push masking from registers to stores
2022-06-26 optional delay on WDCM
2022-06-26 missing commits
2022-07-23 non-hardwired clock domain (for NuBusFPGA)
2022-07-24 vmsize in MiB not KiB (thread at http://mail-index.netbsd.org/port-sparc/2022/02/27/msg002432.html)
2022-08-15 Replace engine-based Jareth by VexRiscv-based 'Jareth' based on NuBusFPGA's goblin accel; also shorten some Forth name to avoid namespace issues.
2022-08-15 preliminary EXA support for new Goblin Accel ; still some issues
2022-08-15 some EXA fix (off-screen solid) ; still an issue in the copy code (could be firmware?)
2022-08-21 more bugfixes for EXA
2022-08-27 debug stuff cleanup
2022-08-27 byte-swap the FB
2022-09-03 For some reason, the dkdriver needs open/close otherwise we can't mount / when booting from sdcard
2022-09-03 fix (probably partial) to support SS IPX (and probably other similar sun4c)
2022-10-08 IRQ update for NuBusFPGA, TBC w/ SBusFPGA
2022-10-09 named parameters for more compatibility
2022-10-09 missing files?
2022-10-31 typoe
2022-10-31 fix sdram irq polarity (to align with NuBusFPGA modifications)
2022-10-31 move some files to a new common submodules
2022-10-31 move to shared goblin
2022-10-31 move blit_goblin to common
2022-10-31 wb_master moved to common
2022-10-31 update common
2022-11-04 commit patch for newer Litex
2022-12-11 typos
2023-02-26 add preliminary support for PROM-in-flash-NOR using a custom PMod
2023-08-21 fixes
2023-09-16 license
2023-09-19 more V1.3
2023-09-20 logo
2023-09-21 minor upd
2023-09-23 details
2023-10-07 missing connection (no impact, connected elsewhere)
